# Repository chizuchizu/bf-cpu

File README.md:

# BFProcessor project

Brainf\*\*kを実行する自作CPUを作成しています。

# ディレクトリ構成

```
.
├── docs       ドキュメント
├── src        FPGAのハードウェア記述コード(gowinで開くことを想定している)
│   └── board       Tang Nano 9K Board の ソースコード
├── schematic  回路図、PCB基板図 (KiCAD ver.8で開くことを想定している)
└── logic      論理回路図 (Logisim Evolutionを開くことを想定している)
```

# 謝辞

このプロジェクトは2024年6月から[サイボウズ・ラボユース](https://labs.cybozu.co.jp/youth.html)の支援を受けて開発しています。

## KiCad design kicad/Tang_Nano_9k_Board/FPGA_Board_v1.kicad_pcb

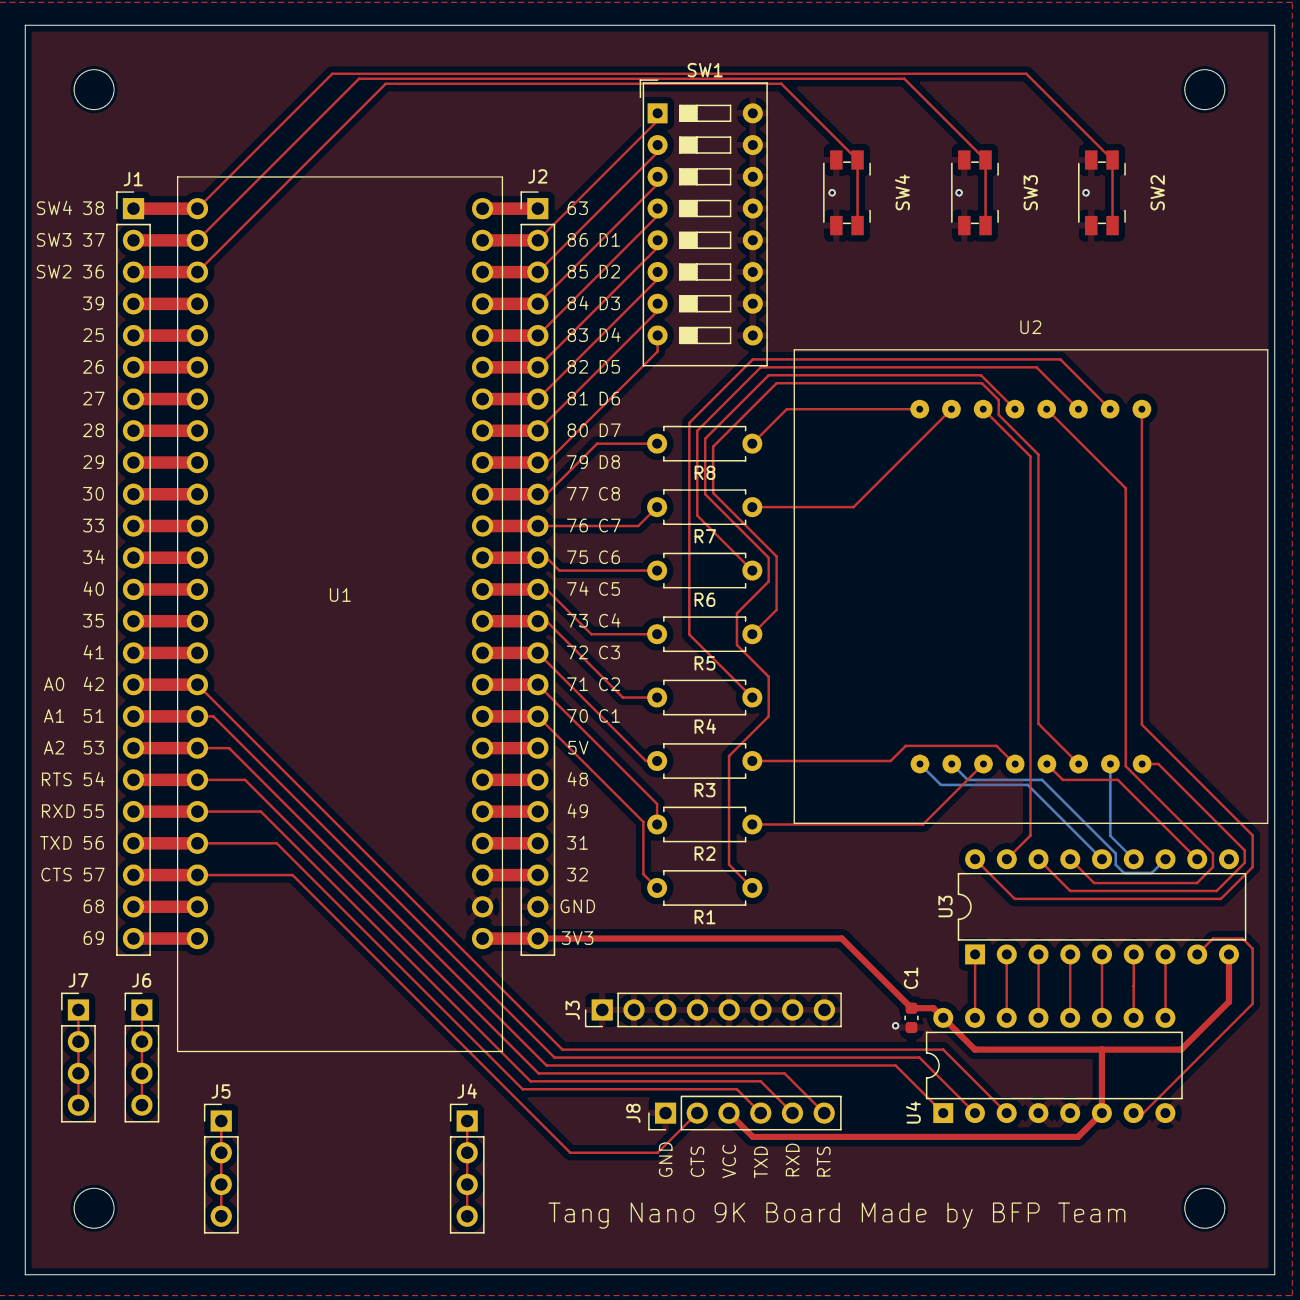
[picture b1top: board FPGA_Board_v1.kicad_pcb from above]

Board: 2 copper layers, 100.0 x 100.0 mm, 29 parts (0 on the bottom side), 76 nets.

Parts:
C1: 0.1μF; C_0603_1608Metric
H1, H2, H3, H4: MountingHole; MountingHole_3.2mm_M3
J1, J2: Conn_01x24; PinHeader_1x24_P2.54mm_Vertical
J3: Conn_01x08; PinHeader_1x08_P2.54mm_Vertical
J4, J5, J6, J7: Conn_01x04; PinHeader_1x04_P2.54mm_Vertical
J8: Conn_01x06; PinHeader_1x06_P2.54mm_Vertical
R1, R2, R3, R4, R5, R6, R7, R8: 750; R_Axial_DIN0207_L6.3mm_D2.5mm_P7.62mm_Horizontal
SW1: SW_DIP_x08; SW_DIP_SPSTx08_Slide_9.78x22.5mm_W7.62mm_P2.54mm
SW2, SW3, SW4: SW_Push; Panasonic_EVQPUJ_EVQPUA
U1: Tang_Nano_9K
U2: OSL641501-BX
U3: TBD62786APG; DIP-18_W7.62mm
U4: 74HC138; CERDIP-16_W7.62mm_SideBrazed

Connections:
+3V3: C1.1, J2.24, J8.3, U1.25 (3V3), U3.9 (COMMON), U4.6 (E2), U4.16 (VCC)
/A0: J1.18, U1.18 (PIN53), U4.1 (A0)
/A1: J1.17, U1.17 (PIN51), U4.2 (A1)
/A2: J1.16, U1.16 (PIN42), U4.3 (A2)
/C1: J2.17, R1.2, U1.32 (HDMI_PIN70)
/C2: J2.16, R2.2, U1.33 (HDMI_PIN71)
/C3: J2.15, R3.2, U1.34 (HDMI_PIN72)
/C4: J2.14, R4.2, U1.35 (HDMI_PIN73)
/C5: J2.13, R5.2, U1.36 (HDMI_PIN74)
/C6: J2.12, R6.2, U1.37 (HDMI_PIN75)
/C7: J2.11, R7.2, U1.38 (PIN76)
/C8: J2.10, R8.2, U1.39 (PIN77)
/CTS: J1.22, J8.2, U1.22 (PIN57)
/RTS: J1.19, J8.6, U1.19 (PIN54)
/RXD: J1.20, J8.5, U1.20 (PIN55)
/TXD: J1.21, J8.4, U1.21 (PIN56)
GND: C1.2, J2.23, J3.1, J3.2, J3.3, J3.4, J3.5, J3.6, J3.7, J3.8, J8.1, SW1.9, SW1.10, SW1.11, SW1.12, SW1.13, SW1.14, SW1.15, SW1.16, SW2.2, SW3.2, SW4.2, U1.26 (GND), U3.10 (GND), U4.4 (~E0), U4.5 (~E1), U4.8 (GND)
unnamed: J1.1, SW2.1, U1.1 (PIN38)
unnamed: J1.2, SW3.1, U1.2 (PIN37)
unnamed: J1.3, SW4.1, U1.3 (PIN36)
unnamed: J1.4, U1.4 (PIN39)
unnamed: J1.5, U1.5 (PIN25)
unnamed: J1.6, U1.6 (PIN26)
unnamed: J1.7, U1.7 (PIN27)
unnamed: J1.8, U1.8 (PIN28)
unnamed: J1.9, U1.9 (PIN29)
unnamed: J1.10, U1.10 (PIN30)
unnamed: J1.11, U1.11 (PIN33)
unnamed: J1.12, U1.12 (PIN34)
unnamed: J1.13, U1.13 (PIN40)
unnamed: J1.14, U1.14 (PIN35)
unnamed: J1.15, U1.15 (PIN41)
unnamed: J1.23, U1.23 (HDMI_PIN68)
unnamed: J1.24, U1.24 (HDMI_PIN69)
unnamed: J2.1, U1.48 (PIN63)
unnamed: J2.2, SW1.1, U1.47 (PIN86)
unnamed: J2.3, SW1.2, U1.46 (PIN85)
unnamed: J2.4, SW1.3, U1.45 (PIN84)
unnamed: J2.5, SW1.4, U1.44 (PIN83)
unnamed: J2.6, SW1.5, U1.43 (PIN82)
unnamed: J2.7, SW1.6, U1.42 (PIN81)
unnamed: J2.8, SW1.7, U1.41 (PIN80)
unnamed: J2.9, SW1.8, U1.40 (PIN79)
unnamed: J2.18, U1.31 (5V)
unnamed: J2.19, U1.30 (PIN48)
unnamed: J2.20, U1.29 (PIN49)
unnamed: J2.21, U1.28 (PIN31)
unnamed: J2.22, U1.27 (PIN32)
unnamed: J4.1, J4.2, J4.3, J4.4
unnamed: J5.1, J5.2, J5.3, J5.4
unnamed: J6.1, J6.2, J6.3, J6.4
unnamed: J7.1, J7.2, J7.3, J7.4
unnamed: R1.1, U2.13 (C1)
unnamed: R2.1, U2.3 (C2)
unnamed: R3.1, U2.4 (C3)
unnamed: R4.1, U2.10 (C4)
unnamed: R5.1, U2.6 (C5)
unnamed: R6.1, U2.11 (C6)
unnamed: R7.1, U2.15 (C7)
unnamed: R8.1, U2.16 (C8)
unnamed: U2.9 (R1), U3.18 (O1)
unnamed: U2.14 (R2), U3.17 (O2)
unnamed: U2.8 (R3), U3.16 (O3)
unnamed: U2.12 (R4), U3.15 (O4)
unnamed: U2.1 (R5), U3.14 (O5)
unnamed: U2.7 (R6), U3.13 (O6)
unnamed: U2.2 (R7), U3.12 (O7)
unnamed: U2.5 (R8), U3.11 (O8)
unnamed: U3.1 (I1), U4.15 (~Y0)
unnamed: U3.2 (I2), U4.14 (~Y1)
unnamed: U3.3 (I3), U4.13 (~Y2)
unnamed: U3.4 (I4), U4.12 (~Y3)
unnamed: U3.5 (I5), U4.11 (~Y4)
unnamed: U3.6 (I6), U4.10 (~Y5)
unnamed: U3.7 (I7), U4.9 (~Y6)
unnamed: U3.8 (I8), U4.7 (~Y7)

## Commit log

2023-11-09 fix typo
2023-11-09 add dairy
2023-11-14 update dairy
2023-11-14 update variable name
2023-11-14 update docs
2023-11-14 update header
2023-12-03 add logic circuits
2024-01-12 add BF Logic 3
2024-01-12 update instruction set
2024-07-04 update kicad schematic
2024-07-08 add led
2024-07-15 complete FPGA Board tmp
2024-08-09 set footprint
2024-08-12 make library in project
2024-08-12 fix footprint libraly Path
2024-08-12 fix symbols path
2024-08-12 add gowin file
2024-08-14 modify pin number of matrix LED
2024-08-14 making pcb board
2024-08-15 set pcb position
2024-08-21 finish schematic, design PCB board
2024-08-21 Reviewed PCB board
2024-08-22 add the documents how to configure library paths
2024-08-26 modify shematic, shift the UART pin up
2024-08-27 WIP: Add tang nano 9k board docs
2024-08-27 update gitignore
2024-08-30 update: clarify README
2024-08-30 Create LICENSE
2024-08-30 update README acknowledge
2024-08-30 fix markdown link
2024-08-30 rm: dairy
2024-08-30 rm decode.py
2024-08-30 rm unnecessary file in kicad, modify *-lib-table
2024-08-30 modify .gitignore, rm unnecessary file in gowin
2024-09-02 complete Tang Nano 9K Board Document
2024-09-03 Update Tang_Nano_9K_Board.md
    グラフの説明を修正した
2024-09-04 fix docs: minor mistakes
2024-09-04 fix docs: レビュー反映 大きめの話の半分を修正
2024-09-04 fix docs: move exp section to a new file
2024-09-04 fix link
2024-09-04 fix docs: move dir
2024-09-04 mv to README
2024-09-04 fix unsaved change, save images to repogitory
2024-09-04 fix images
2024-09-04 renamed images
2024-09-04 rm vscode setting file
2024-09-05 fix cst file of Tang Nano 9K Board
2024-09-06 update verilog files of Matrix LED dynamic lighting
2024-09-11 Add comment ロジックに理由付け
2024-09-11 Add push & dip switch to BoardTest
2024-09-11 Add プッシュスイッチのフットプリントが枚違っていることの追記
2024-09-11 fix: pin number and drive strength
2024-09-12 add function to remove chattering of push switch
2024-09-13 fix minor mistake
2024-09-13 fix size of counter to avoid chattering
2024-09-20 add testfile for verilog testbench
2024-09-23 fix: conter size 8 -> 7
2024-09-23 rm: output file
2024-09-23 move: gowin to src, kicad to schematic
2024-09-23 add: alu
2024-09-23 fix: bit width
2024-09-23 fix: delete non-blocking
2024-09-23 fix: colon to semicolon
2024-09-23 fix: type miss of decrement
2024-09-23 fix alu constant value and pass the alu test bench
2024-09-23 find latest logisim project
2024-09-23 add decoder only with IO module
2024-09-25 add gate function
2024-11-08 add logicIC directory, 74HC08, 74HC74
2024-11-08 fix missing endmodule in 74HC08
2024-11-08 add logicIC 00,02,04,08,32
2024-11-08 add 74hc161
2024-11-14 add Makefile and 74HC00 testbench, fix module name
2024-11-14 add 74HC02 testbench, fix module name
2024-11-14 add 74HC04 testbench
2024-11-14 add 74HC08 testbench
2024-11-14 add 74HC32 testbench
2024-11-14 add 74HC74 testbench, fix module name, port name
2024-12-02 renamed 74HCxx to logic_74HCxx
2024-12-02 fix misstake
2024-12-02 fix mistake of typo
2024-12-02 add rule to ignore .vcd and .out in testvench
2024-12-02 update Makefile; execute all .out file when make
2024-12-02 fix 74HC74testbench: delete clk2
2024-12-03 create: logic_74HC283_tb
2024-12-03 fix: logic_74HC283_tb.sv mistake
2024-12-03 add logic_74HC283.sv
2024-12-03 fix logic_74HC74_tb.sv: remove clk2 parameter, decrease amount of clk1 tick
2024-12-03 change 74HC74testbench: add test in pr = H and clr = H
2024-12-03 change 74HC74: add feature for out and ~out to be both wH in pr = H and clr = H
2024-12-03 change; Makefile execute
2024-12-12 add: logic_74HC273_tb.sv
2024-12-12 add 74HC161 testbench
2024-12-12 fix 74HC273 testbench: add temp 74HC273 module
2024-12-23 change 74HC273_tb: to check if the value is still 0 after clr
2024-12-23 change 74HC273: behavior after clr
2024-12-23 fix: add case if internal register is undefined and clr is on
2024-12-23 fix: change initiallization process to change register directly
2024-12-23 change 74HC273: n_clr in sensitivirity list to negedge
2024-12-23 fix 74HC161 testbench: have clock work, release rst
2024-12-23 add 74HC161 module
2024-12-26 add logic_74HC541: test bench
2024-12-26 create: logic_74HC541 module
2024-12-26 change directory: move logicIC to bfcpu/logicIC, add new Makefile to access all Makefile in subdirectory from Makefile in tobdirectory
2024-12-27 fix Makefile: include test bench file in source
2024-12-27 create ALU: test bench, alu.sv has error
2024-12-27 add general register test bench
2025-01-02 add logicIC module: add include guard
2025-01-02 change Makefile: add module directory
2025-01-02 fix: Explicit port names in ICmodule instance
2025-01-02 create: zero_detector test bench
2025-01-02 change: add test if input and output is equal
2025-01-02 add general register
2025-01-02 fix: zero_detector_tb mistake, add zero_detector module
2025-01-02 add equal detector testbench
2025-01-06 add equal detector
2025-01-06 change general register: variants with naming rule
2025-01-06 fix: Naming convention
2025-01-17 add:decoder_remake, change:reg to negative logic, change:pin name
2025-01-17 remove: rm old alu file
2025-01-19 add stack pointer testbench
2025-01-19 fix stack pointer tb: inactivate n_clr not to remain clr
2025-01-19 fix stack pointr testbench:change zero detector into equal detector
2025-01-19 add stack pointer module
2025-02-10 add bram primitive testbench
2025-02-10 fix bram primitive tb: set rst down after rst check
2025-02-10 fix bram primitive tb: set ce = 1, wre = 0 when read data
2025-02-10 add bram primitive
2025-02-10 create: decoder test bench
2025-02-27 fix: add include guard
2025-02-27 add asynchronous ram testbench
2025-03-09 fix asynchronous ram testbench: set data_in high impedance when ce controled
2025-03-09 add asynchronous ram
2025-03-12 add waveform of Data RAM, Stack RAM, Instruction RAM
2025-03-17 fix waveform: change H or L to 1 or 0 in order to delay signals
2025-03-18 add data ram testbench
2025-03-18 fix data ram testbench: remove n_ce due to always GND
2025-03-18 fix data ram testbench: fix wrong expectation
2025-03-18 fix data ram testbench: fix wrong expectatio
2025-03-18 change data ram testbench: remove clk
2025-03-18 change data tam testbench: fix test_dff output
2025-03-18 add address register test
2025-03-18 add address register
2025-03-19 add instruction ram testbench
2025-03-19 add instruction ram, switch
2025-03-20 add program counter testbench
2025-03-21 fix program counter: clear data after switched to manual and switched to non-manual
2025-03-21 add program counter
2025-03-21 add stack ram testbench
2025-03-21 fix stack ram testbench: change expected output to High-Z when output is unenabled
2025-03-21 fix Makefile: add instruction_ram program_counter in testall
2025-03-21 add stack ram
2025-03-21 change data ram: set or between ld and n_we on n_g of input 3-state-buffer
2025-03-22 add divider testbench
2025-03-22 add divider
2025-03-22 add waveform generator testbench
2025-03-22 change divider: add comment
2025-03-22 fix waveform generator testbench: change test_dff to correct position
2025-03-22 add waveform generator
2025-03-23 add: decoder module
